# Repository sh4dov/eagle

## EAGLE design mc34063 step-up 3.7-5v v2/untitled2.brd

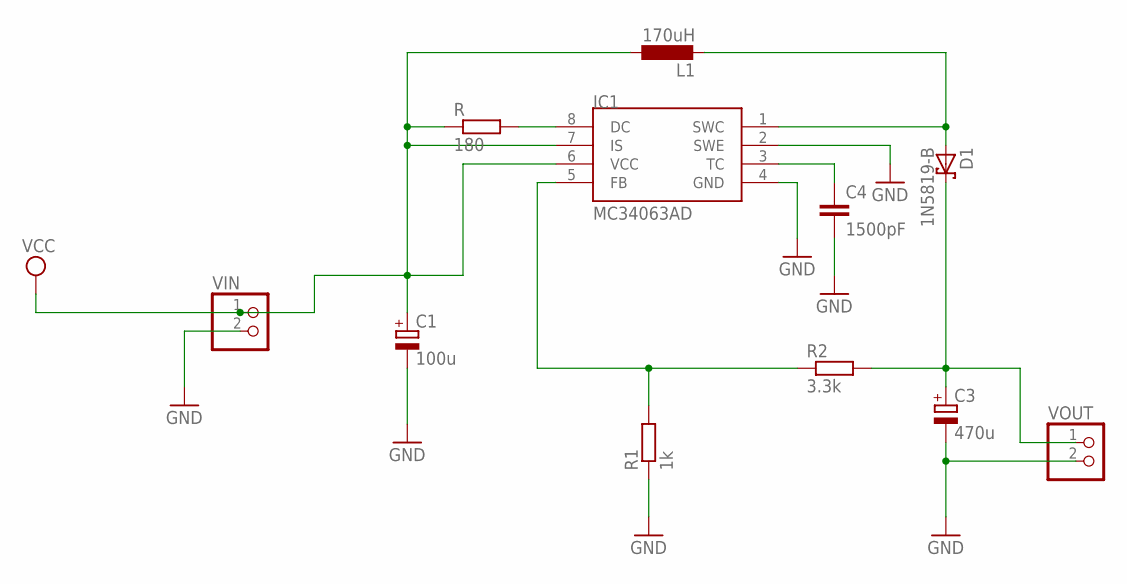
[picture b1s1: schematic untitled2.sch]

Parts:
C1: 100u; E2,5-6E
C3: 470u; E5-10,5
C4: 1500pF; C1206
D1: 1N5819-B; DO41-7.6
IC1: MC34063AD; SOIC8
L1: 170uH; 0204/5
R: 180; R0805W
R1: 1k; R1206W
R2: 3.3k; R1206W
VIN: PINHD-1X2; 1X02
VOUT: PINHD-1X2; 1X02

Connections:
GND: C1.-, C3.-, C4.2, IC1.2 (SWE), IC1.4 (GND), R1.1, VIN.2, VOUT.2
unnamed: D1.A, IC1.1 (SWC), L1.2
unnamed: C3.+, D1.C, R2.2, VOUT.1
unnamed: C4.1, IC1.3 (TC)
unnamed: IC1.5 (FB), R1.2, R2.1
unnamed: IC1.8 (DC), R.2
VCC: C1.+, IC1.6 (VCC), IC1.7 (IS), L1.1, R.1, VIN.1

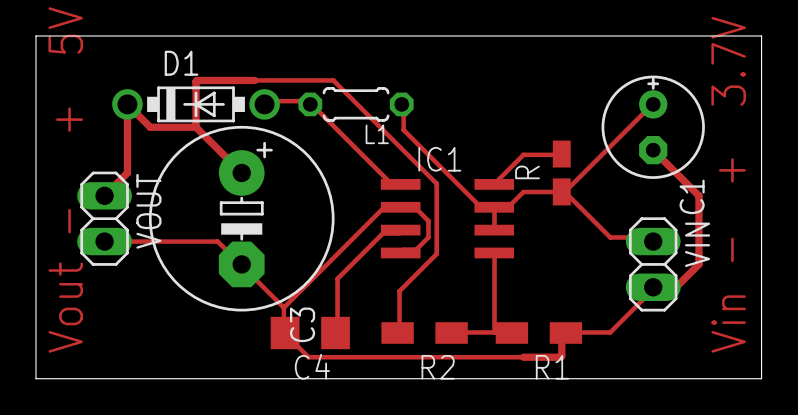
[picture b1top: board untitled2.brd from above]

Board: 2 copper layers, 40.3 x 19.0 mm, 11 parts (0 on the bottom side), 7 nets.

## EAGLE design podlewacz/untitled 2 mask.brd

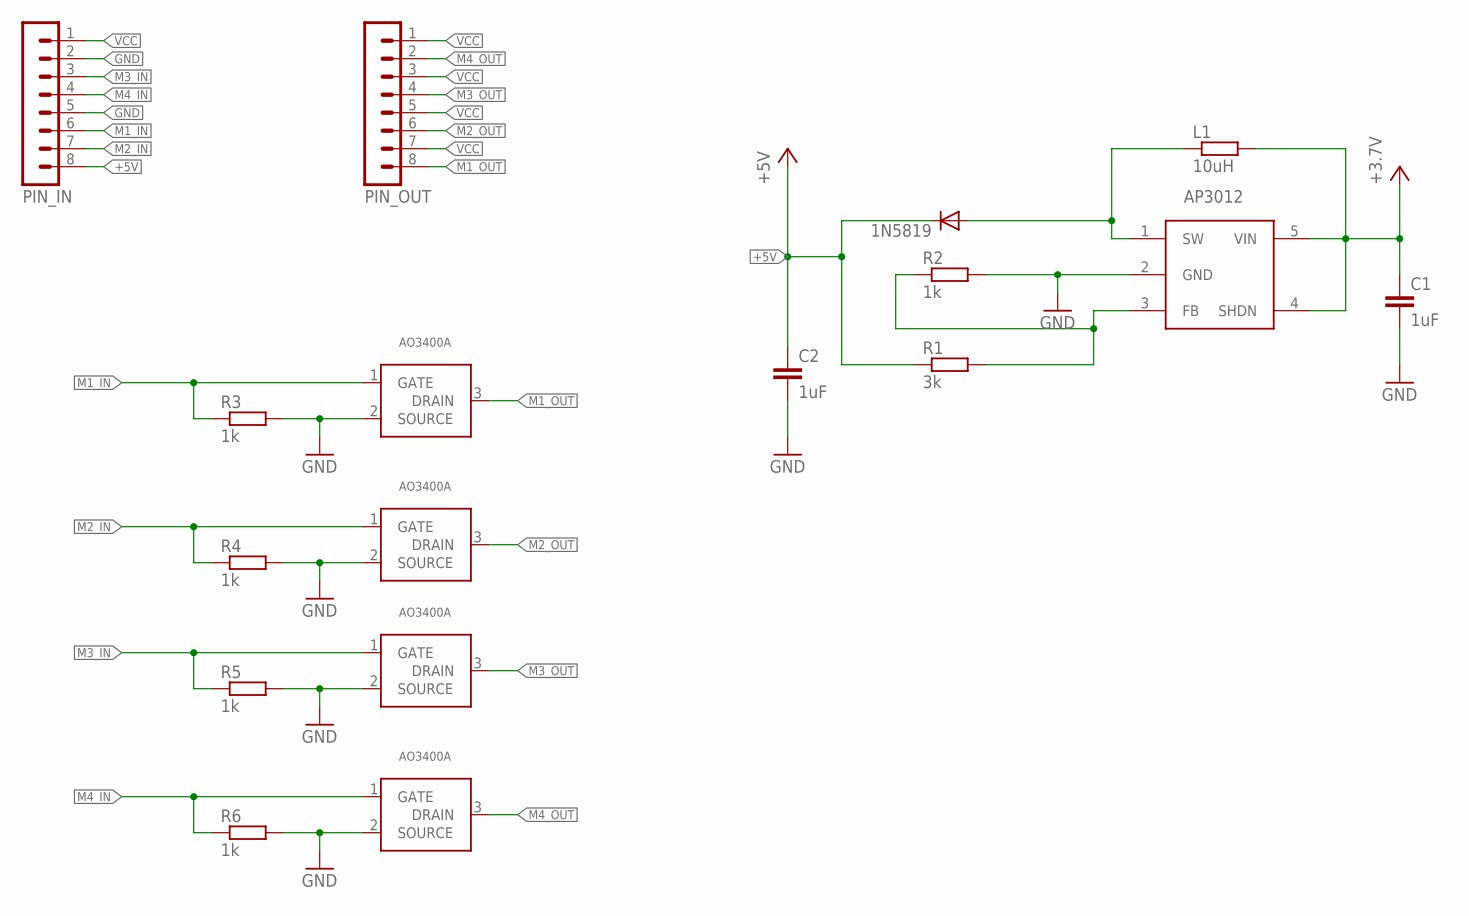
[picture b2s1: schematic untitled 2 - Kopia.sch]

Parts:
1N5819: DIODE-DO214AC; DO214AC
C1, C2: 1uF; C1206
L1: 10uH; R0805
MOSFET1, MOSFET2, MOSFET3, MOSFET4: AO3400A; SOT-23
PIN_IN: MA08-1
PIN_OUT: MA08-1
R1: 3k; R1206
R2, R3, R4, R5, R6: 1k; R1206
U$1: AP3012; SOT-23-5

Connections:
+5V: 1N5819.C, C2.1, PIN_IN.8, R1.1
GND: C1.2, C2.2, MOSFET1.2 (SOURCE), MOSFET2.2 (SOURCE), MOSFET3.2 (SOURCE), MOSFET4.2 (SOURCE), PIN_IN.2, PIN_IN.5, R2.2, R3.2, R4.2, R5.2, R6.2, U$1.2 (GND)
M1_IN: MOSFET1.1 (GATE), PIN_IN.6, R3.1
M1_OUT: MOSFET1.3 (DRAIN), PIN_OUT.8
M2_IN: MOSFET2.1 (GATE), PIN_IN.7, R4.1
M2_OUT: MOSFET2.3 (DRAIN), PIN_OUT.6
M3_IN: MOSFET3.1 (GATE), PIN_IN.3, R5.1
M3_OUT: MOSFET3.3 (DRAIN), PIN_OUT.4
M4_IN: MOSFET4.1 (GATE), PIN_IN.4, R6.1
M4_OUT: MOSFET4.3 (DRAIN), PIN_OUT.2
unnamed: 1N5819.A, L1.1, U$1.1 (SW)
unnamed: R1.2, R2.1, U$1.3 (FB)
VCC: C1.1, L1.2, PIN_IN.1, PIN_OUT.1, PIN_OUT.3, PIN_OUT.5, PIN_OUT.7, U$1.4 (SHDN), U$1.5 (VIN)

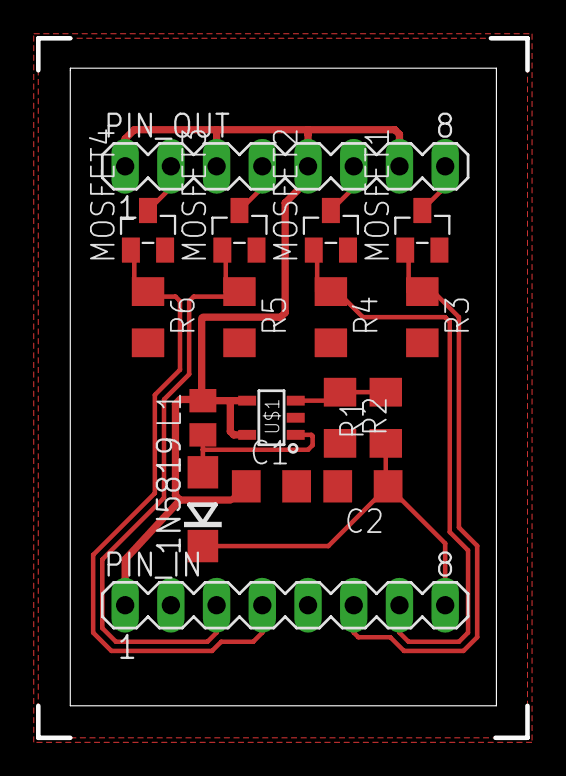
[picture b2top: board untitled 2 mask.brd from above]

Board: 2 copper layers, 23.7 x 35.4 mm, 17 parts (0 on the bottom side), 13 nets.

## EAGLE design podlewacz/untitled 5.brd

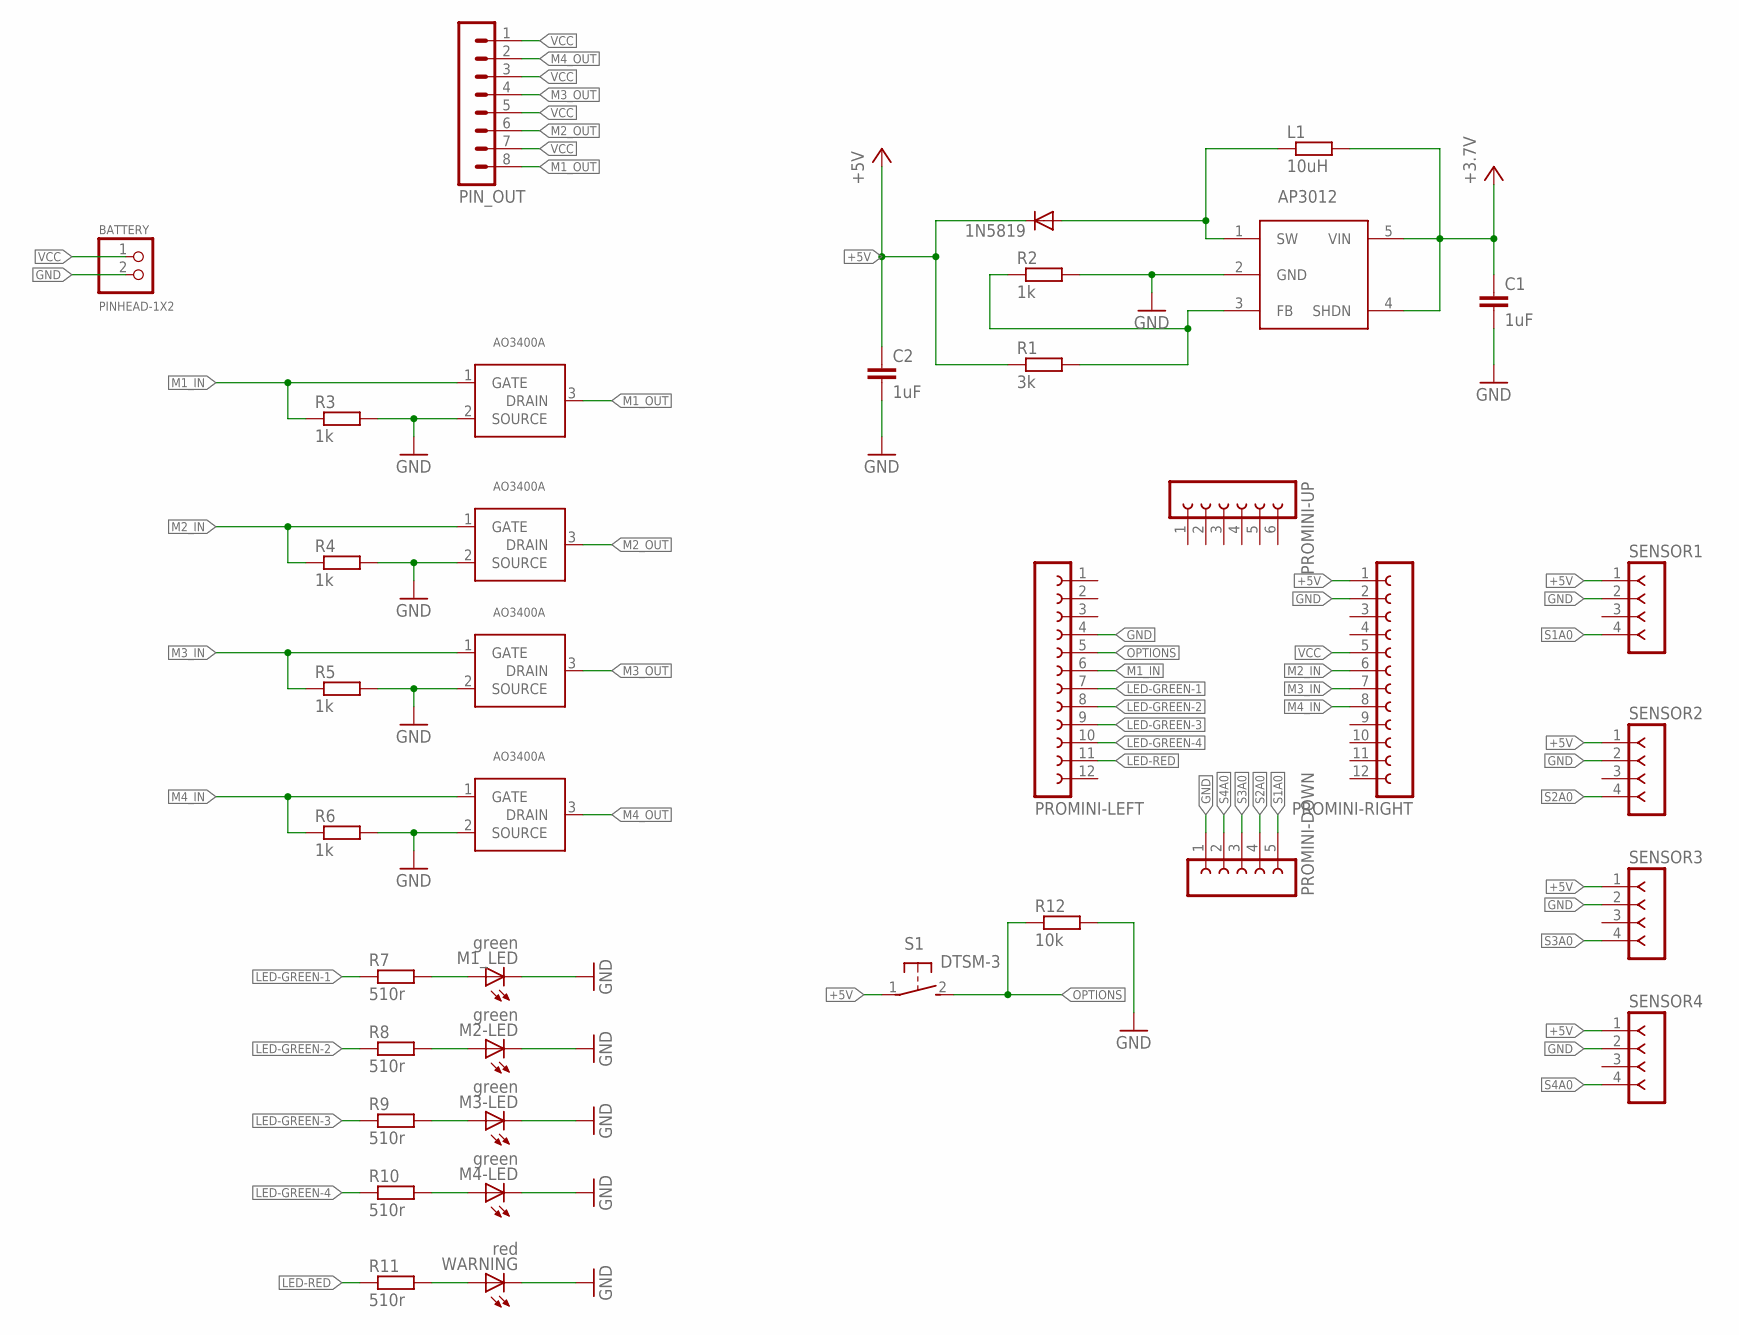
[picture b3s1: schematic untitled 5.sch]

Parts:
1N5819: DIODE-DO214AC; DO214AC
BATTERY: PINHEAD-1X2; PIHEAD-1X2
C1, C2: 1uF; C1206
L1: 10uH; R0805
M1_LED, M2-LED, M3-LED, M4-LED: green; CHIP-LED0805
MOSFET1, MOSFET2, MOSFET3, MOSFET4: AO3400A; SOT-23
PIN_OUT: MA08-1
PROMINI-DOWN: FE05-1
PROMINI-LEFT: FE12-1; FE12
PROMINI-RIGHT: FE12-1; FE12
PROMINI-UP: FE06-1; FE06
R1: 3k; R1206
R2, R3, R4, R5, R6: 1k; R1206
R7, R8, R9, R10, R11: 510r; M0805
R12: 10k; R1206
S1: DTSM-3
SENSOR1, SENSOR2, SENSOR3, SENSOR4: F-1X04-SIP-100-32Y; SIP-100-04-32Y
U$1: AP3012; SOT-23-5
WARNING: red; CHIP-LED0805

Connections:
+5V: 1N5819.C, C2.1, PROMINI-RIGHT.1, R1.1, S1.1, SENSOR1.1, SENSOR2.1, SENSOR3.1, SENSOR4.1
GND: BATTERY.2, C1.2, C2.2, M1_LED.C, M2-LED.C, M3-LED.C, M4-LED.C, MOSFET1.2 (SOURCE), MOSFET2.2 (SOURCE), MOSFET3.2 (SOURCE), MOSFET4.2 (SOURCE), PROMINI-DOWN.1, PROMINI-LEFT.4, PROMINI-RIGHT.2, R2.2, R3.2, R4.2, R5.2, R6.2, R12.2, SENSOR1.2, SENSOR2.2, SENSOR3.2, SENSOR4.2, U$1.2 (GND), WARNING.C
LED-GREEN-1: PROMINI-LEFT.7, R7.1
LED-GREEN-2: PROMINI-LEFT.8, R8.1
LED-GREEN-3: PROMINI-LEFT.9, R9.1
LED-GREEN-4: PROMINI-LEFT.10, R10.1
LED-RED: PROMINI-LEFT.11, R11.1
M1_IN: MOSFET1.1 (GATE), PROMINI-LEFT.6, R3.1
M1_OUT: MOSFET1.3 (DRAIN), PIN_OUT.8
M2_IN: MOSFET2.1 (GATE), PROMINI-RIGHT.6, R4.1
M2_OUT: MOSFET2.3 (DRAIN), PIN_OUT.6
M3_IN: MOSFET3.1 (GATE), PROMINI-RIGHT.7, R5.1
M3_OUT: MOSFET3.3 (DRAIN), PIN_OUT.4
M4_IN: MOSFET4.1 (GATE), PROMINI-RIGHT.8, R6.1
M4_OUT: MOSFET4.3 (DRAIN), PIN_OUT.2
unnamed: 1N5819.A, L1.1, U$1.1 (SW)
unnamed: R1.2, R2.1, U$1.3 (FB)
unnamed: R11.2, WARNING.A
unnamed: M4-LED.A, R10.2
unnamed: M3-LED.A, R9.2
unnamed: M2-LED.A, R8.2
unnamed: M1_LED.A, R7.2
OPTIONS: PROMINI-LEFT.5, R12.1, S1.2
S1A0: PROMINI-DOWN.5, SENSOR1.4
S2A0: PROMINI-DOWN.4, SENSOR2.4
S3A0: PROMINI-DOWN.3, SENSOR3.4
S4A0: PROMINI-DOWN.2, SENSOR4.4
VCC: BATTERY.1, C1.1, L1.2, PIN_OUT.1, PIN_OUT.3, PIN_OUT.5, PIN_OUT.7, PROMINI-RIGHT.5, U$1.4 (SHDN), U$1.5 (VIN)

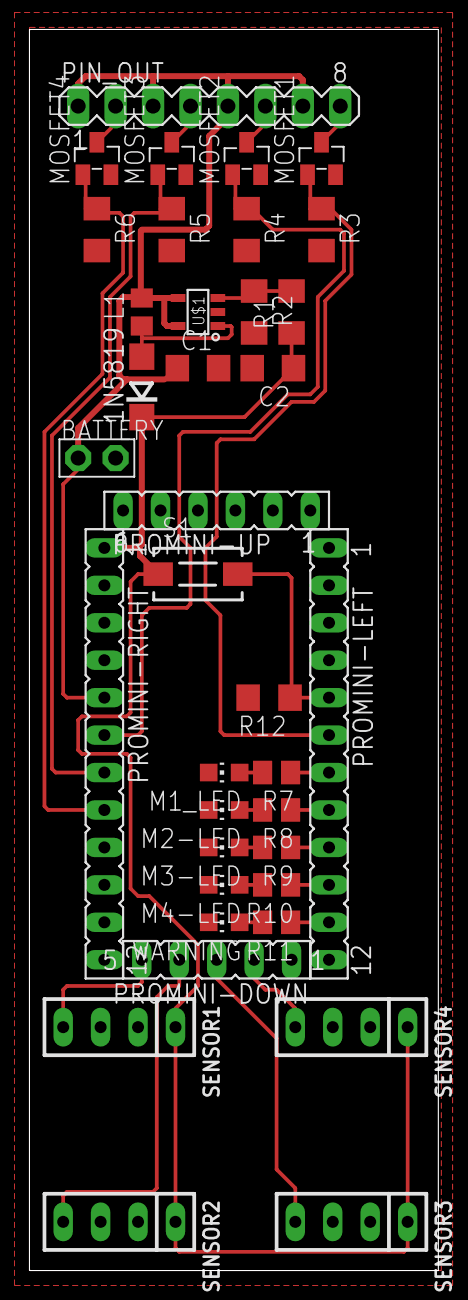
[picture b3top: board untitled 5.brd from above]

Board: 2 copper layers, 27.7 x 84.2 mm, 37 parts (0 on the bottom side), 28 nets.

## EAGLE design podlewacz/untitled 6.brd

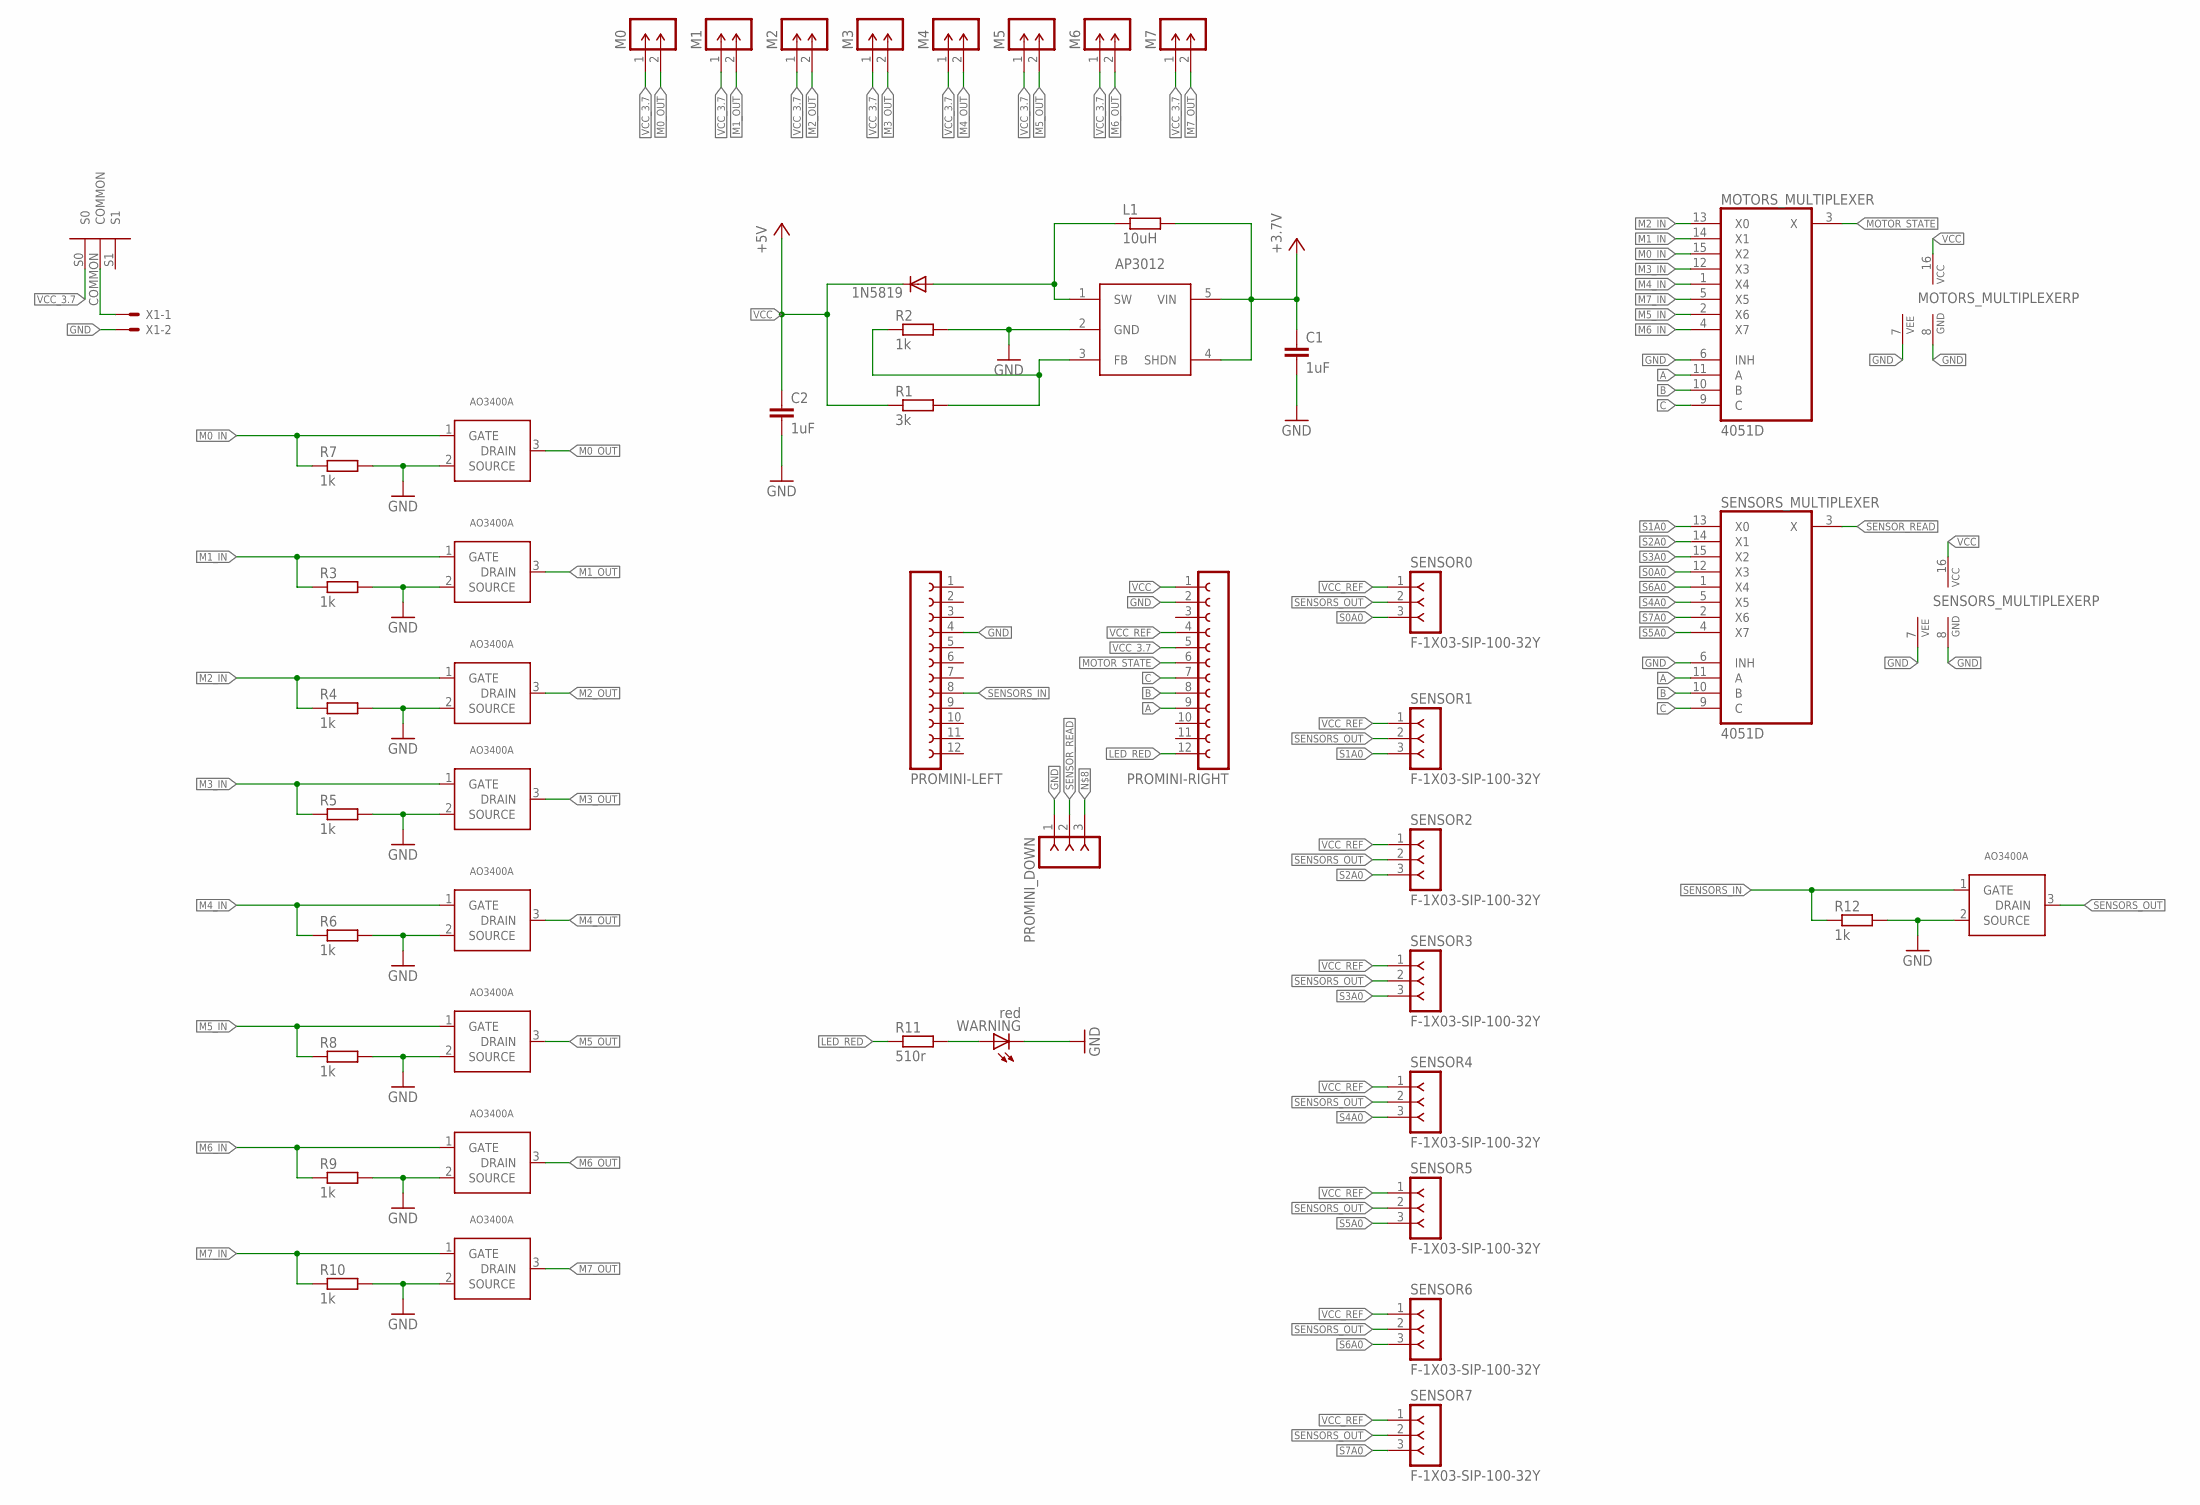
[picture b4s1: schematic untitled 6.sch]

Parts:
1N5819: DIODE-DO214AC; DO214AC
C1, C2: 1uF; C1206
L1: 10uH; R0805
M0, M1, M2, M3, M4, M5, M6, M7: M-1X02-SIP-100-32Y; SIP-100-02-32Y
MOSFET0, MOSFET1, MOSFET2, MOSFET3, MOSFET4, MOSFET5, MOSFET6, MOSFET7, MOSFET8: AO3400A; SOT-23
MOTORS_MULTIPLEXER: 4051D; SO16
PROMINI-LEFT: FE12-1; FE12
PROMINI-RIGHT: FE12-1; FE12
PROMINI_DOWN: F-1X03-SIP-100-32Y; SIP-100-03-32Y
R1: 3k; R1206
R2, R3, R4, R5, R6, R7, R8, R9, R10, R12: 1k; R1206
R11: 510r; M0805
SENSOR0, SENSOR1, SENSOR2, SENSOR3, SENSOR4, SENSOR5, SENSOR6, SENSOR7: F-1X03-SIP-100-32Y; SIP-100-03-32Y
SENSORS_MULTIPLEXER: 4051D; SO16
U$1: AP3012; SOT-23-5
U$2: SPDT_SLIDE_SWITCH_2_PITCH
WARNING: red; CHIP-LED0805
X1: JST-XH-02-PIN-LONG-PAD; JST-XH-02-PACKAGE-LONG-PAD

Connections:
A: MOTORS_MULTIPLEXER.11 (A), PROMINI-RIGHT.9, SENSORS_MULTIPLEXER.11 (A)
B: MOTORS_MULTIPLEXER.10 (B), PROMINI-RIGHT.8, SENSORS_MULTIPLEXER.10 (B)
C: MOTORS_MULTIPLEXER.9 (C), PROMINI-RIGHT.7, SENSORS_MULTIPLEXER.9 (C)
GND: C1.2, C2.2, MOSFET0.2 (SOURCE), MOSFET1.2 (SOURCE), MOSFET2.2 (SOURCE), MOSFET3.2 (SOURCE), MOSFET4.2 (SOURCE), MOSFET5.2 (SOURCE), MOSFET6.2 (SOURCE), MOSFET7.2 (SOURCE), MOSFET8.2 (SOURCE), MOTORS_MULTIPLEXER.6 (INH), MOTORS_MULTIPLEXER.7 (VEE), MOTORS_MULTIPLEXER.8 (GND), PROMINI-LEFT.4, PROMINI-RIGHT.2, PROMINI_DOWN.1, R2.2, R3.2, R4.2, R5.2, R6.2, R7.2, R8.2, R9.2, R10.2, R12.2, SENSORS_MULTIPLEXER.6 (INH), SENSORS_MULTIPLEXER.7 (VEE), SENSORS_MULTIPLEXER.8 (GND), U$1.2 (GND), WARNING.C, X1.2
LED_RED: PROMINI-RIGHT.12, R11.1
M0_IN: MOSFET0.1 (GATE), MOTORS_MULTIPLEXER.15 (X2), R7.1
M0_OUT: M0.2, MOSFET0.3 (DRAIN)
M1_IN: MOSFET1.1 (GATE), MOTORS_MULTIPLEXER.14 (X1), R3.1
M1_OUT: M1.2, MOSFET1.3 (DRAIN)
M2_IN: MOSFET2.1 (GATE), MOTORS_MULTIPLEXER.13 (X0), R4.1
M2_OUT: M2.2, MOSFET2.3 (DRAIN)
M3_IN: MOSFET3.1 (GATE), MOTORS_MULTIPLEXER.12 (X3), R5.1
M3_OUT: M3.2, MOSFET3.3 (DRAIN)
M4_IN: MOSFET4.1 (GATE), MOTORS_MULTIPLEXER.1 (X4), R6.1
M4_OUT: M4.2, MOSFET4.3 (DRAIN)
M5_IN: MOSFET5.1 (GATE), MOTORS_MULTIPLEXER.2 (X6), R8.1
M5_OUT: M5.2, MOSFET5.3 (DRAIN)
M6_IN: MOSFET6.1 (GATE), MOTORS_MULTIPLEXER.4 (X7), R9.1
M6_OUT: M6.2, MOSFET6.3 (DRAIN)
M7_IN: MOSFET7.1 (GATE), MOTORS_MULTIPLEXER.5 (X5), R10.1
M7_OUT: M7.2, MOSFET7.3 (DRAIN)
MOTOR_STATE: MOTORS_MULTIPLEXER.3 (X), PROMINI-RIGHT.6
unnamed: 1N5819.A, L1.1, U$1.1 (SW)
unnamed: R1.2, R2.1, U$1.3 (FB)
unnamed: R11.2, WARNING.A
unnamed: U$2.COMMON, X1.1
S0A0: SENSOR0.3, SENSORS_MULTIPLEXER.12 (X3)
S1A0: SENSOR1.3, SENSORS_MULTIPLEXER.13 (X0)
S2A0: SENSOR2.3, SENSORS_MULTIPLEXER.14 (X1)
S3A0: SENSOR3.3, SENSORS_MULTIPLEXER.15 (X2)
S4A0: SENSOR4.3, SENSORS_MULTIPLEXER.5 (X5)
S5A0: SENSOR5.3, SENSORS_MULTIPLEXER.4 (X7)
S6A0: SENSOR6.3, SENSORS_MULTIPLEXER.1 (X4)
S7A0: SENSOR7.3, SENSORS_MULTIPLEXER.2 (X6)
SENSORS_IN: MOSFET8.1 (GATE), PROMINI-LEFT.8, R12.1
SENSORS_OUT: MOSFET8.3 (DRAIN), SENSOR0.2, SENSOR1.2, SENSOR2.2, SENSOR3.2, SENSOR4.2, SENSOR5.2, SENSOR6.2, SENSOR7.2
SENSOR_READ: PROMINI_DOWN.2, SENSORS_MULTIPLEXER.3 (X)
VCC: 1N5819.C, C2.1, MOTORS_MULTIPLEXER.16 (VCC), PROMINI-RIGHT.1, R1.1, SENSORS_MULTIPLEXER.16 (VCC)
VCC_3.7: C1.1, L1.2, M0.1, M1.1, M2.1, M3.1, M4.1, M5.1, M6.1, M7.1, PROMINI-RIGHT.5, U$1.4 (SHDN), U$1.5 (VIN), U$2.S0
VCC_REF: PROMINI-RIGHT.4, SENSOR0.1, SENSOR1.1, SENSOR2.1, SENSOR3.1, SENSOR4.1, SENSOR5.1, SENSOR6.1, SENSOR7.1

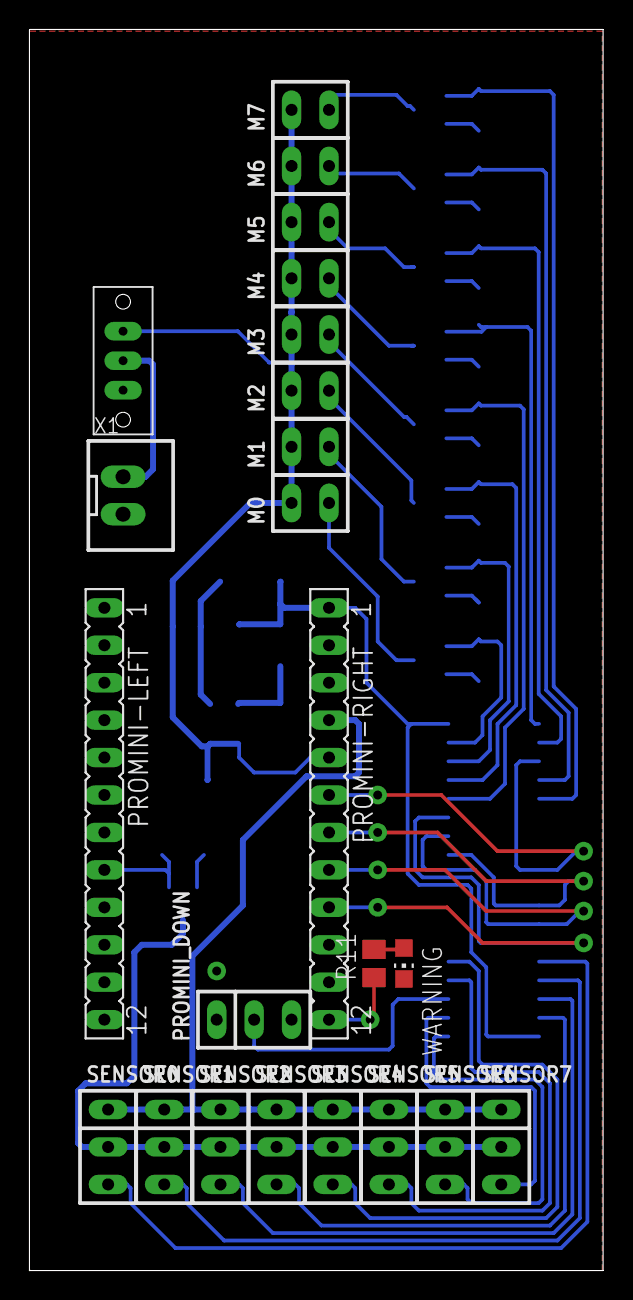
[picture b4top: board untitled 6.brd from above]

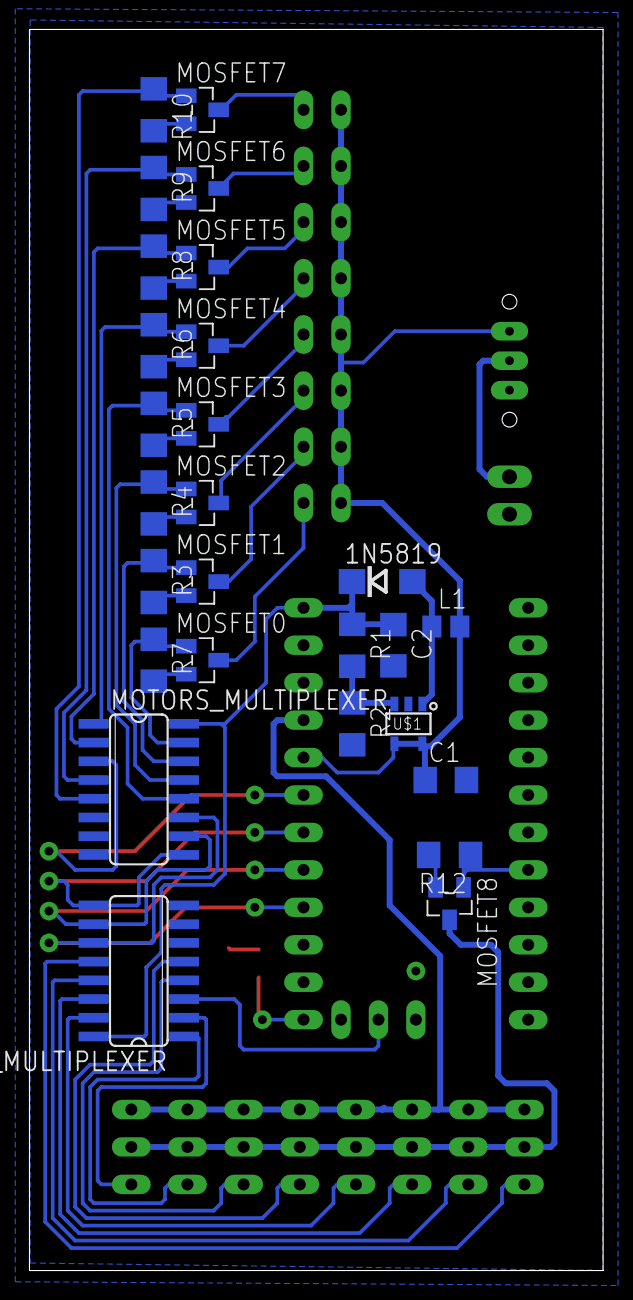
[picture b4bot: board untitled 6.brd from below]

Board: 2 copper layers, 38.9 x 84.2 mm, 50 parts (27 on the bottom side), 40 nets.

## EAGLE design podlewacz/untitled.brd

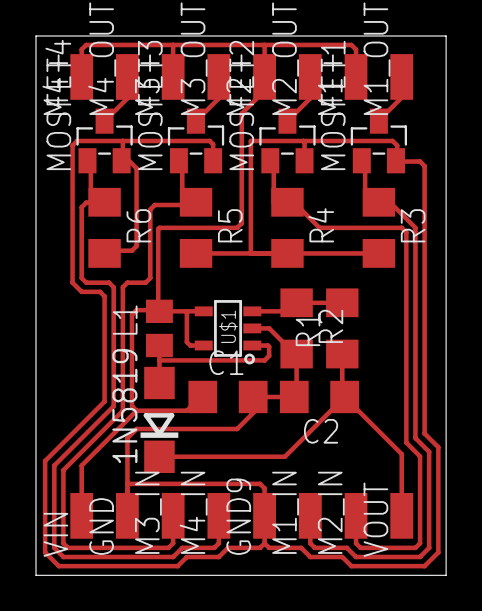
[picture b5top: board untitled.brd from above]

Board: 2 copper layers, 22.8 x 30.0 mm, 31 parts (0 on the bottom side), 13 nets.

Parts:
1N5819: DO214AC
C1, C2: 1uF; C1206
GND, GND9: SMD1,27-2,54
L1: 10uH; R0805
M1+, M1_IN, M1_OUT, M2+, M2_IN, M2_OUT, M3+, M3_IN, M3_OUT, M4+, M4_IN, M4_OUT: SMD1,27-2,54
MOSFET1, MOSFET2, MOSFET3, MOSFET4: AO3400A; SOT-23
R1: 3k; R1206
R2, R3, R4, R5, R6: 1k; R1206
U$1: SOT-23-5
VIN: SMD1,27-2,54
VOUT: SMD1,27-2,54

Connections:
+5V: 1N5819.C, C2.1, R1.1, VOUT.1
GND: C1.2, C2.2, GND.1, GND9.1, MOSFET1.2, MOSFET2.2, MOSFET3.2, MOSFET4.2, R2.2, R3.2, R4.2, R5.2, R6.2, U$1.2
unnamed: 1N5819.A, L1.1, U$1.1
unnamed: M4_IN.1, MOSFET4.1, R6.1
unnamed: R1.2, R2.1, U$1.3
unnamed: M3_IN.1, MOSFET3.1, R5.1
unnamed: M2_IN.1, MOSFET2.1, R4.1
unnamed: M1_IN.1, MOSFET1.1, R3.1
unnamed: M1_OUT.1, MOSFET1.3
unnamed: M2_OUT.1, MOSFET2.3
unnamed: M3_OUT.1, MOSFET3.3
unnamed: M4_OUT.1, MOSFET4.3
VCC: C1.1, L1.2, M1+.1, M2+.1, M3+.1, M4+.1, U$1.4, U$1.5, VIN.1

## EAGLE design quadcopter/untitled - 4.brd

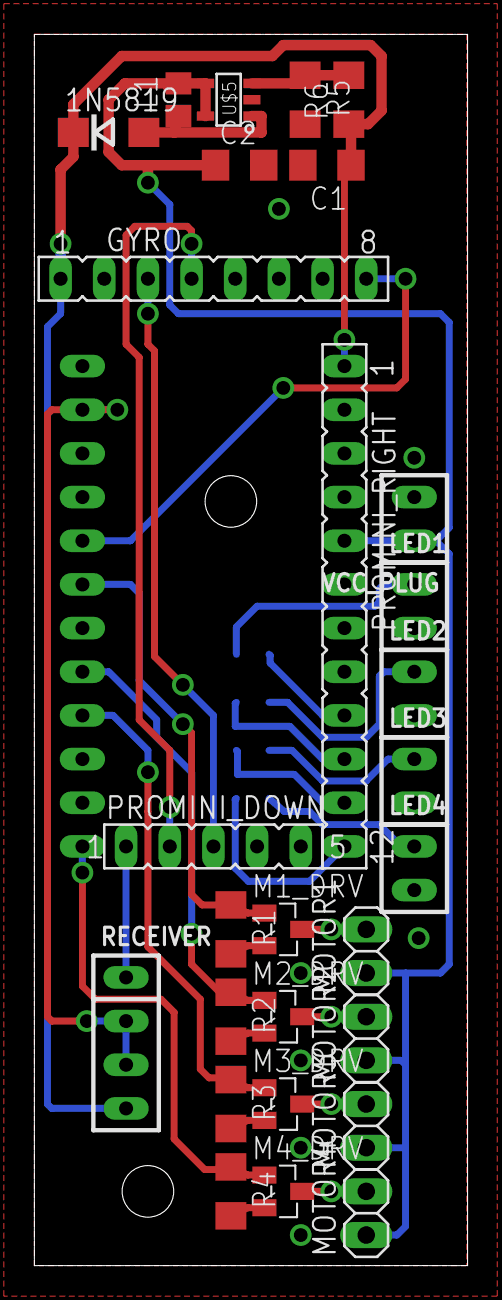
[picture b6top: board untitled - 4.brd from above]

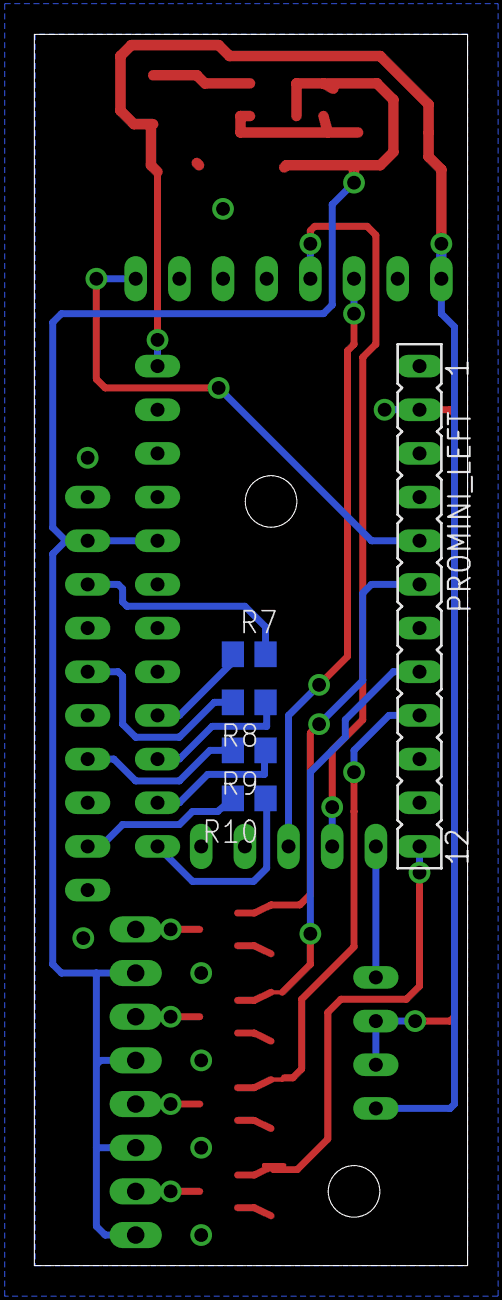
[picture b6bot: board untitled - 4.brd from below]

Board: 2 copper layers, 25.2 x 71.6 mm, 33 parts (5 on the bottom side), 26 nets.

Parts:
1N5819: DO214AC
C1, C2: 1uF; C1206
GYRO: FE08
L1: 10uH; R0805
LED1, LED2, LED3, LED4: SIP-100-02-32Y
M1_DRV, M2_DRV, M3_DRV, M4_DRV: AO3400A; SOT-23
MOTOR1, MOTOR2, MOTOR3, MOTOR4: 1X02
PROMINI_DOWN: FE05-1
PROMINI_LEFT: FE12
PROMINI_RIGHT: FE12
R1, R2, R3, R4, R5: 1k; R1206
R6: 3k; R1206
R7, R8, R9, R10: 510; R0805
RECEIVER: F-1X04-SIP-100-32Y; SIP-100-04-32Y
U$5: SOT-23-5
VCC_PLUG: M-1X02-SIP-100-32Y; SIP-100-02-32Y

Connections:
10: PROMINI_RIGHT.12, R10.1
11: PROMINI_RIGHT.11, R9.1
12: PROMINI_RIGHT.10, R8.1
13: PROMINI_RIGHT.9, R7.1
+5V: 1N5819.C, C1.1, GYRO.1, PROMINI_RIGHT.1, R6.1, RECEIVER.4
GND: C1.2, C2.2, GYRO.2, LED1.2, LED2.2, LED3.2, LED4.2, M1_DRV.2, M2_DRV.2, M3_DRV.2, M4_DRV.2, PROMINI_RIGHT.2, R1.2, R2.2, R3.2, R4.2, R5.2, U$5.2, VCC_PLUG.2
INT: GYRO.8, PROMINI_LEFT.5
M1_IN: M1_DRV.1, PROMINI_LEFT.6, R1.1
M1_OUT: M1_DRV.3, MOTOR1.2
M2_IN: M2_DRV.1, PROMINI_LEFT.8, R2.1
M2_OUT: M2_DRV.3, MOTOR2.2
M3_IN: M3_DRV.1, PROMINI_LEFT.9, R3.1
M3_OUT: M3_DRV.3, MOTOR3.2
M4_IN: M4_DRV.1, PROMINI_LEFT.12, R4.1
M4_OUT: M4_DRV.3, MOTOR4.2
unnamed: LED4.1, R10.2
unnamed: 1N5819.A, L1.1, U$5.1
unnamed: R5.1, R6.2, U$5.3
unnamed: LED3.1, R9.2
unnamed: LED2.1, R8.2
unnamed: LED1.1, R7.2
RECEIVER_GND: PROMINI_DOWN.1, RECEIVER.1
RX: PROMINI_LEFT.2, RECEIVER.2, RECEIVER.3
SCL: GYRO.3, PROMINI_DOWN.3
SDA: GYRO.4, PROMINI_DOWN.2
VCC: C2.1, L1.2, MOTOR1.1, MOTOR2.1, MOTOR3.1, MOTOR4.1, PROMINI_RIGHT.5, U$5.4, U$5.5, VCC_PLUG.1

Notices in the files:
parts and their libraries:
con-headers-jp: Copyright (C) 2008, Bob Starr
